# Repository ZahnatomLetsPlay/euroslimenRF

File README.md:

# euroslimenRF
SlimeVR tracker using a Nordic Semi nRF52 series MCU. It's about the same size as a 1€ coin

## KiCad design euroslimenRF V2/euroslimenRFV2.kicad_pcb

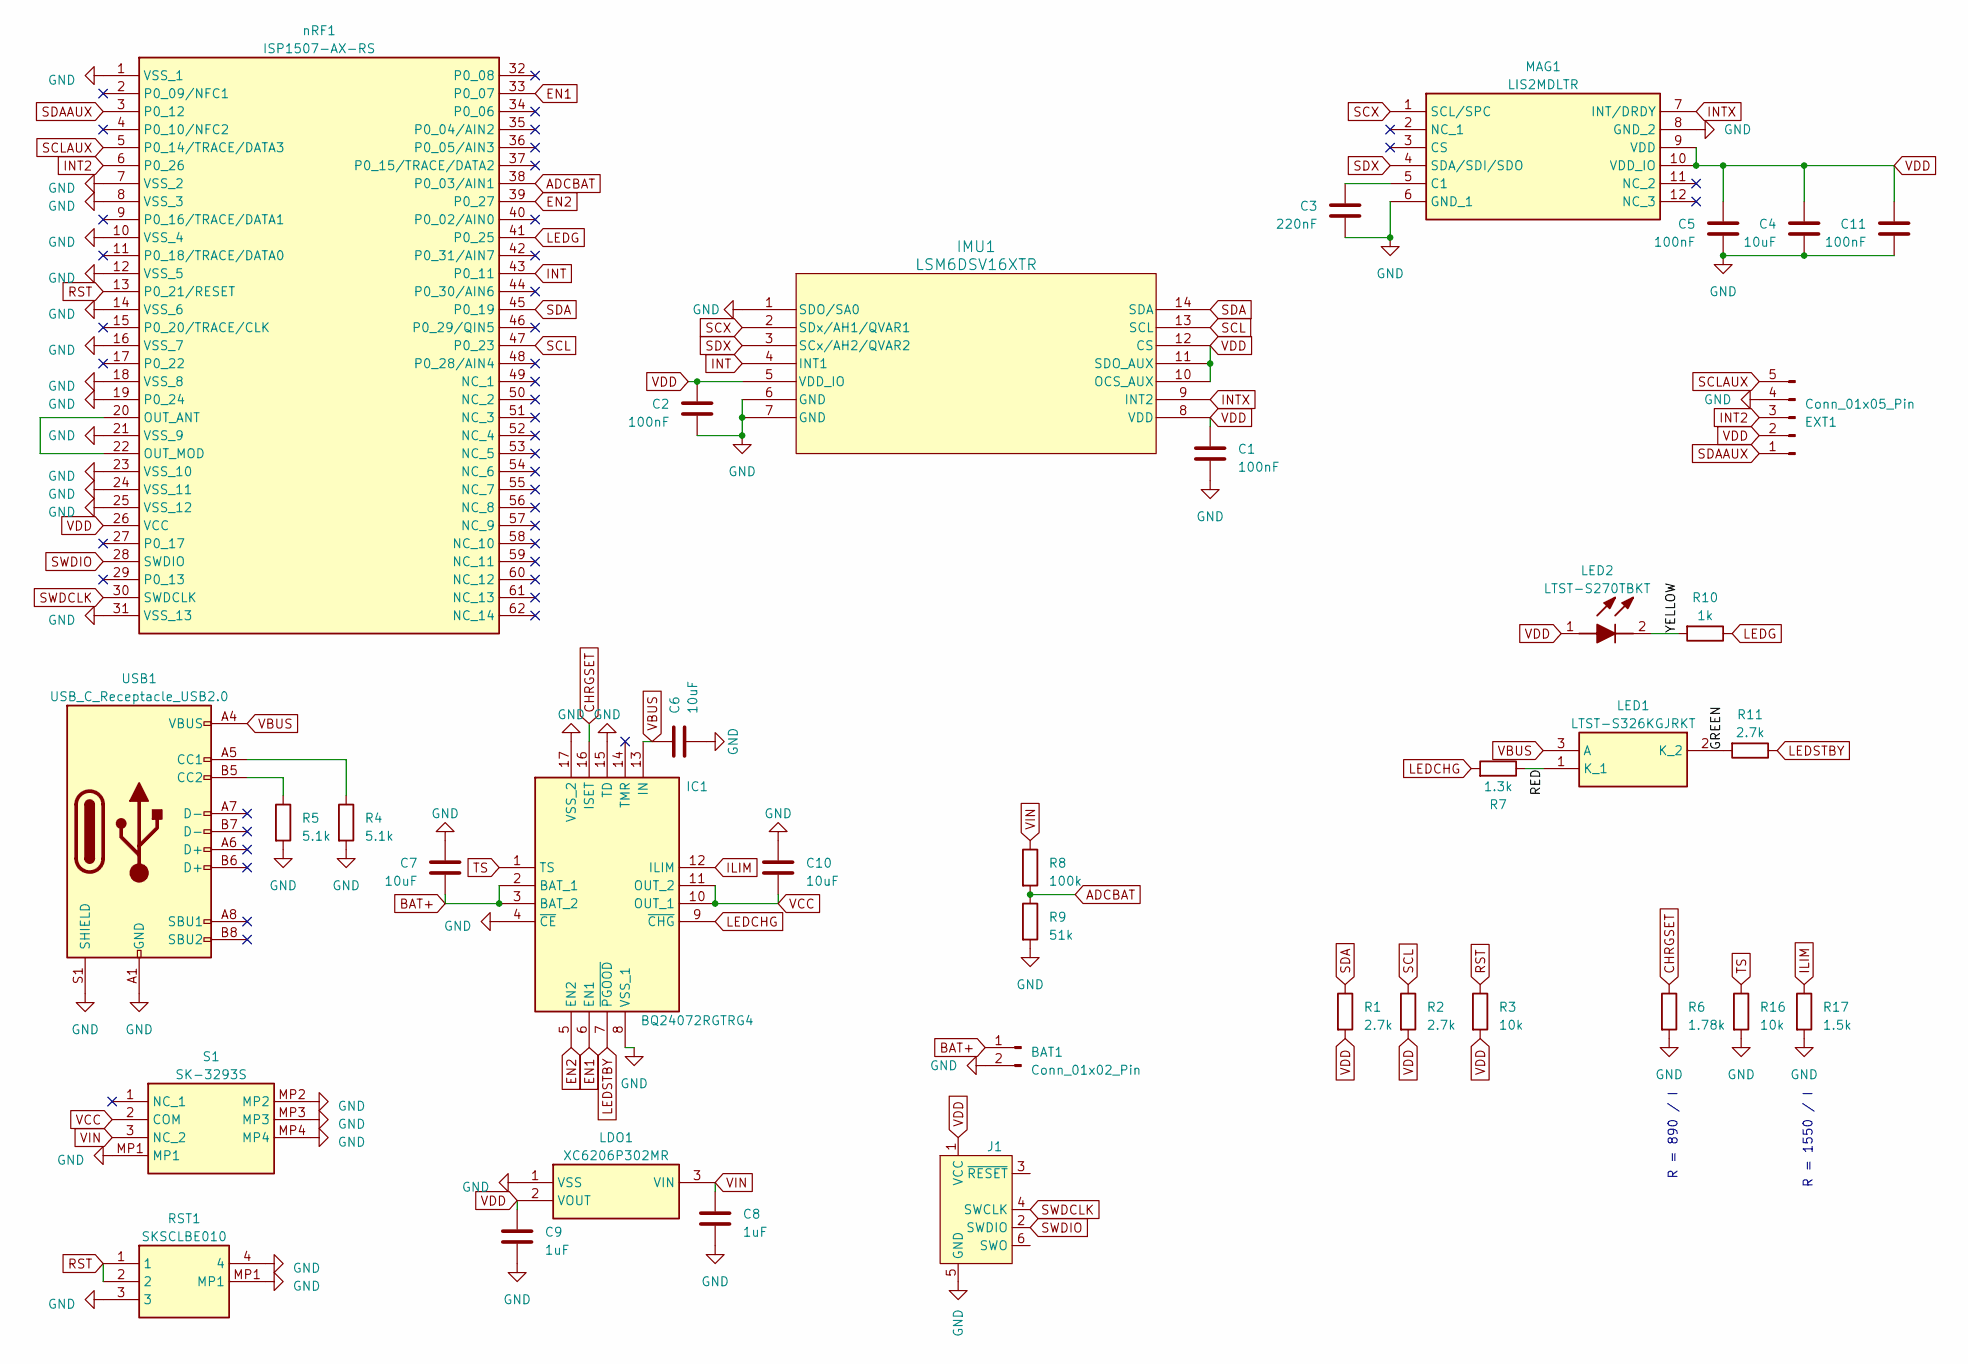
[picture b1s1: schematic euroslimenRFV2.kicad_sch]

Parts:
BAT1: Conn_01x02_Pin; JST_PH_S2B-PH-K_1x02_P2.00mm_Horizontal
C1, C2, C5, C11: 100nF; C_0402_1005Metric
C3: 220nF; C_0402_1005Metric
C4, C6, C7, C10: 10uF; C_0402_1005Metric
C8, C9: 1uF; C_0402_1005Metric
EXT1: Conn_01x05_Pin; JST_PH_S5B-PH-K_1x05_P2.00mm_Horizontal
IC1: BQ24072RGTRG4; QFN50P300X300X100-17N-D; Manufacturer_Part_Number BQ24072RGTRG4
IMU1: LSM6DSV16XTR; LGA14L_LSM6_STM
J1: Conn_ARM_SWD_TagConnect_TC2030-NL; Tag-Connect_TC2030-IDC-NL_2x03_P1.27mm_Vertical
LDO1: XC6206P302MR; SOT95P280X130-3N; Manufacturer_Part_Number XC6206P302MR; Mouser Part Number N/A
LED1: LTST-S326KGJRKT; Manufacturer_Part_Number LTST-S326KGJRKT; Mouser Part Number 859-LTST-S326KGJRKT
LED2: LTST-S270TBKT; LTSTS270TBKT; Manufacturer_Part_Number LTST-S270TBKT; Mouser Part Number 859-LTST-S270TBKT
MAG1: LIS2MDLTR; LGA-12; Manufacturer_Part_Number LIS2MDLTR; Mouser Part Number 511-LIS2MDLTR
R1, R2, R11: 2.7k; R_0402_1005Metric
R3, R16: 10k; R_0402_1005Metric
R4, R5: 5.1k; R_0402_1005Metric
R6: 1.78k; R_0402_1005Metric
R7: 1.3k; R_0402_1005Metric
R8: 100k; R_0402_1005Metric
R9: 51k; R_0402_1005Metric
R10: 1k; R_0402_1005Metric
R17: 1.5k; R_0402_1005Metric
RST1: SKSCLBE010; Manufacturer_Part_Number SKSCLBE010; Mouser Part Number 688-SKSCLBE010
S1: SK-3293S; SK3293S; Manufacturer_Part_Number SK-3293S
USB1: USB_C_Receptacle_USB2.0; USB_C_Receptacle_GCT_USB4105-xx-A_16P_TopMnt_Horizontal
nRF1: ISP1507-AX-RS; ISP1507AXRS; Manufacturer_Part_Number ISP1507-AX-RS; Mouser Part Number 359-ISP1507-AX-RS

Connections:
/GREEN: LED1.2 (K_2), R11.2
/RED: LED1.1 (K_1), R7.1
/YELLOW: LED2.2 (K), R10.2
ADCBAT: R8.2, R9.1, nRF1.38 (P0_03/AIN1)
BAT+: BAT1.1, C7.1, IC1.2 (BAT_1), IC1.3 (BAT_2)
CC1: R4.1, USB1.A5 (CC1)
CC2: R5.1, USB1.B5 (CC2)
CHRGSET: IC1.16 (ISET), R6.1
EN1: IC1.6 (EN1), nRF1.33 (P0_07)
EN2: IC1.5 (EN2), nRF1.39 (P0_27)
GND: BAT1.2, C1.2, C2.2, C3.2, C4.2, C5.2, C6.1, C7.2, C8.2, C9.2, C10.2, C11.2, EXT1.4, IC1.4 (~CE), IC1.8 (VSS_1), IC1.15 (TD), IC1.17 (VSS_2), IMU1.1 (SDO/SA0), IMU1.6 (GND), IMU1.7 (GND), J1.5 (GND), LDO1.1 (VSS), MAG1.6 (GND_1), MAG1.8 (GND_2), R4.2, R5.2, R6.2, R9.2, R16.2, R17.2, RST1.3, RST1.4, RST1.MP1, S1.MP1, S1.MP2, S1.MP3, S1.MP4, USB1.A1 (GND), USB1.A12 (GND), USB1.B1 (GND), USB1.B12 (GND), USB1.S1 (SHIELD), nRF1.1 (VSS_1), nRF1.7 (VSS_2), nRF1.8 (VSS_3), nRF1.10 (VSS_4), nRF1.12 (VSS_5), nRF1.14 (VSS_6), nRF1.16 (VSS_7), nRF1.18 (VSS_8), nRF1.19 (P0_24), nRF1.21 (VSS_9), nRF1.23 (VSS_10), nRF1.24 (VSS_11), nRF1.25 (VSS_12), nRF1.31 (VSS_13)
ILIM: IC1.12 (ILIM), R17.1
INT: IMU1.4 (INT1), nRF1.43 (P0_11)
INT2: EXT1.3, nRF1.6 (P0_26)
INTX: IMU1.9 (INT2), MAG1.7 (INT/DRDY)
LEDCHG: IC1.9 (~CHG), R7.2
LEDG: R10.1, nRF1.41 (P0_25)
LEDSTBY: IC1.7 (~PGOOD), R11.1
unnamed: C3.1, MAG1.5 (C1)
unnamed: nRF1.20 (OUT_ANT), nRF1.22 (OUT_MOD)
RST: R3.1, RST1.1, RST1.2, nRF1.13 (P0_21/RESET)
SCL: IMU1.13 (SCL), R2.1, nRF1.47 (P0_23)
SCLAUX: EXT1.5, nRF1.5 (P0_14/TRACE/DATA3)
SCX: IMU1.2 (SDx/AH1/QVAR1), MAG1.1 (SCL/SPC)
SDA: IMU1.14 (SDA), R1.1, nRF1.45 (P0_19)
SDAAUX: EXT1.1, nRF1.3 (P0_12)
SDX: IMU1.3 (SCx/AH2/QVAR2), MAG1.4 (SDA/SDI/SDO)
SWDCLK: J1.4 (SWCLK), nRF1.30 (SWDCLK)
SWDIO: J1.2 (SWDIO), nRF1.28 (SWDIO)
TS: IC1.1 (TS), R16.1
VBUS: C6.2, IC1.13 (IN), LED1.3 (A), USB1.A4 (VBUS), USB1.A9 (VBUS), USB1.B4 (VBUS), USB1.B9 (VBUS)
VCC: C10.1, IC1.10 (OUT_1), IC1.11 (OUT_2), S1.2 (COM)

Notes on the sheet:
R = 890 / I
R = 1550 / I

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
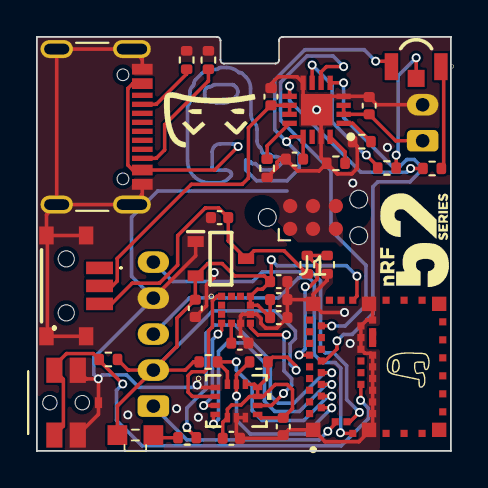
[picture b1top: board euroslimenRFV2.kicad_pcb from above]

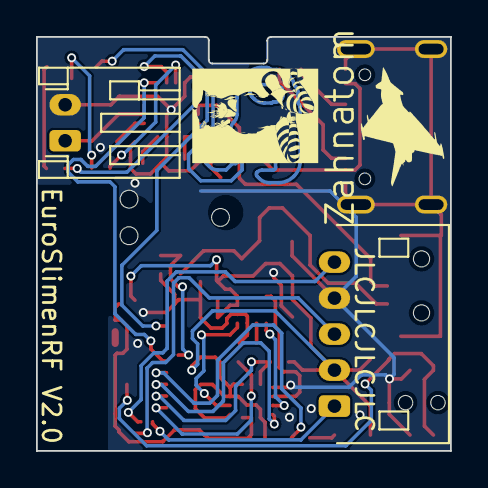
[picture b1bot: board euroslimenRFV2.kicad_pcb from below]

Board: 2 copper layers, 23.0 x 23.0 mm, 38 parts (2 on the bottom side), 34 nets.

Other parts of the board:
GnRF: LOGO

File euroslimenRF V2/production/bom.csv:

Designator,Footprint,Quantity,Value,LCSC Part #
BAT1,JST_PH_S2B-PH-K_1x02_P2.00mm_Horizontal,1,Conn_01x02_Pin,
"C1, C11, C2, C5",0402,4,100nF,
"C10, C4, C6, C7",0402,4,10uF,
C3,0402,1,220nF,
"C8, C9",0402,2,1uF,
EXT1,JST_PH_S5B-PH-K_1x05_P2.00mm_Horizontal,1,Conn_01x05_Pin,
IC1,QFN50P300X300X100-17N-D,1,BQ24072RGTRG4,
IMU1,LGA14L_LSM6_STM,1,LSM6DSV16XTR,
LDO1,SOT95P280X130-3N,1,XC6206P302MR,
LED1,LTST-S326KGJRKT,1,LTST-S326KGJRKT,
LED2,LTSTS270TBKT,1,LTST-S270TBKT,
MAG1,LGA-12,1,LIS2MDLTR,
PROG1,PinHeader_1x03_P2.54mm_Horizontal,1,Conn_01x03_Pin,
"R1, R2",0402,2,2.7k,
R10,0402,1,1k,
R11,0402,1,"2,7k",
"R16, R3",0402,2,10k,
R17,0402,1,1.5k,
"R4, R5",0402,2,5.1k,
R6,0402,1,1.78k,
R7,0402,1,"1,3k",
R8,0402,1,100k,
R9,0402,1,51k,
RST1,SKSCLBE010,1,SKSCLBE010,
S1,SK3293S,1,SK-3293S,
USB1,USB_C_Receptacle_GCT_USB4105-xx-A_16P_TopMnt_Horizontal,1,USB_C_Receptacle_USB2.0,
nRF1,ISP1507AXRS,1,ISP1507-AX-RS,

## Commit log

2023-07-16 V1 with ICM42688-P and MMC5983MA upload
    do not ask about the altium file, idk how to get rid of it
2023-07-16 V2 with LSM6DSV16X and LIS2MDL upload
    dont ask about the altium file here either.
    this board is, so far, only experimental and has not EVER been built.
2023-07-16 Create LICENSE
